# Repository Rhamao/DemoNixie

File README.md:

# DemoNixie
Nouvelle branche du design Android après le merge avec QtBLE.

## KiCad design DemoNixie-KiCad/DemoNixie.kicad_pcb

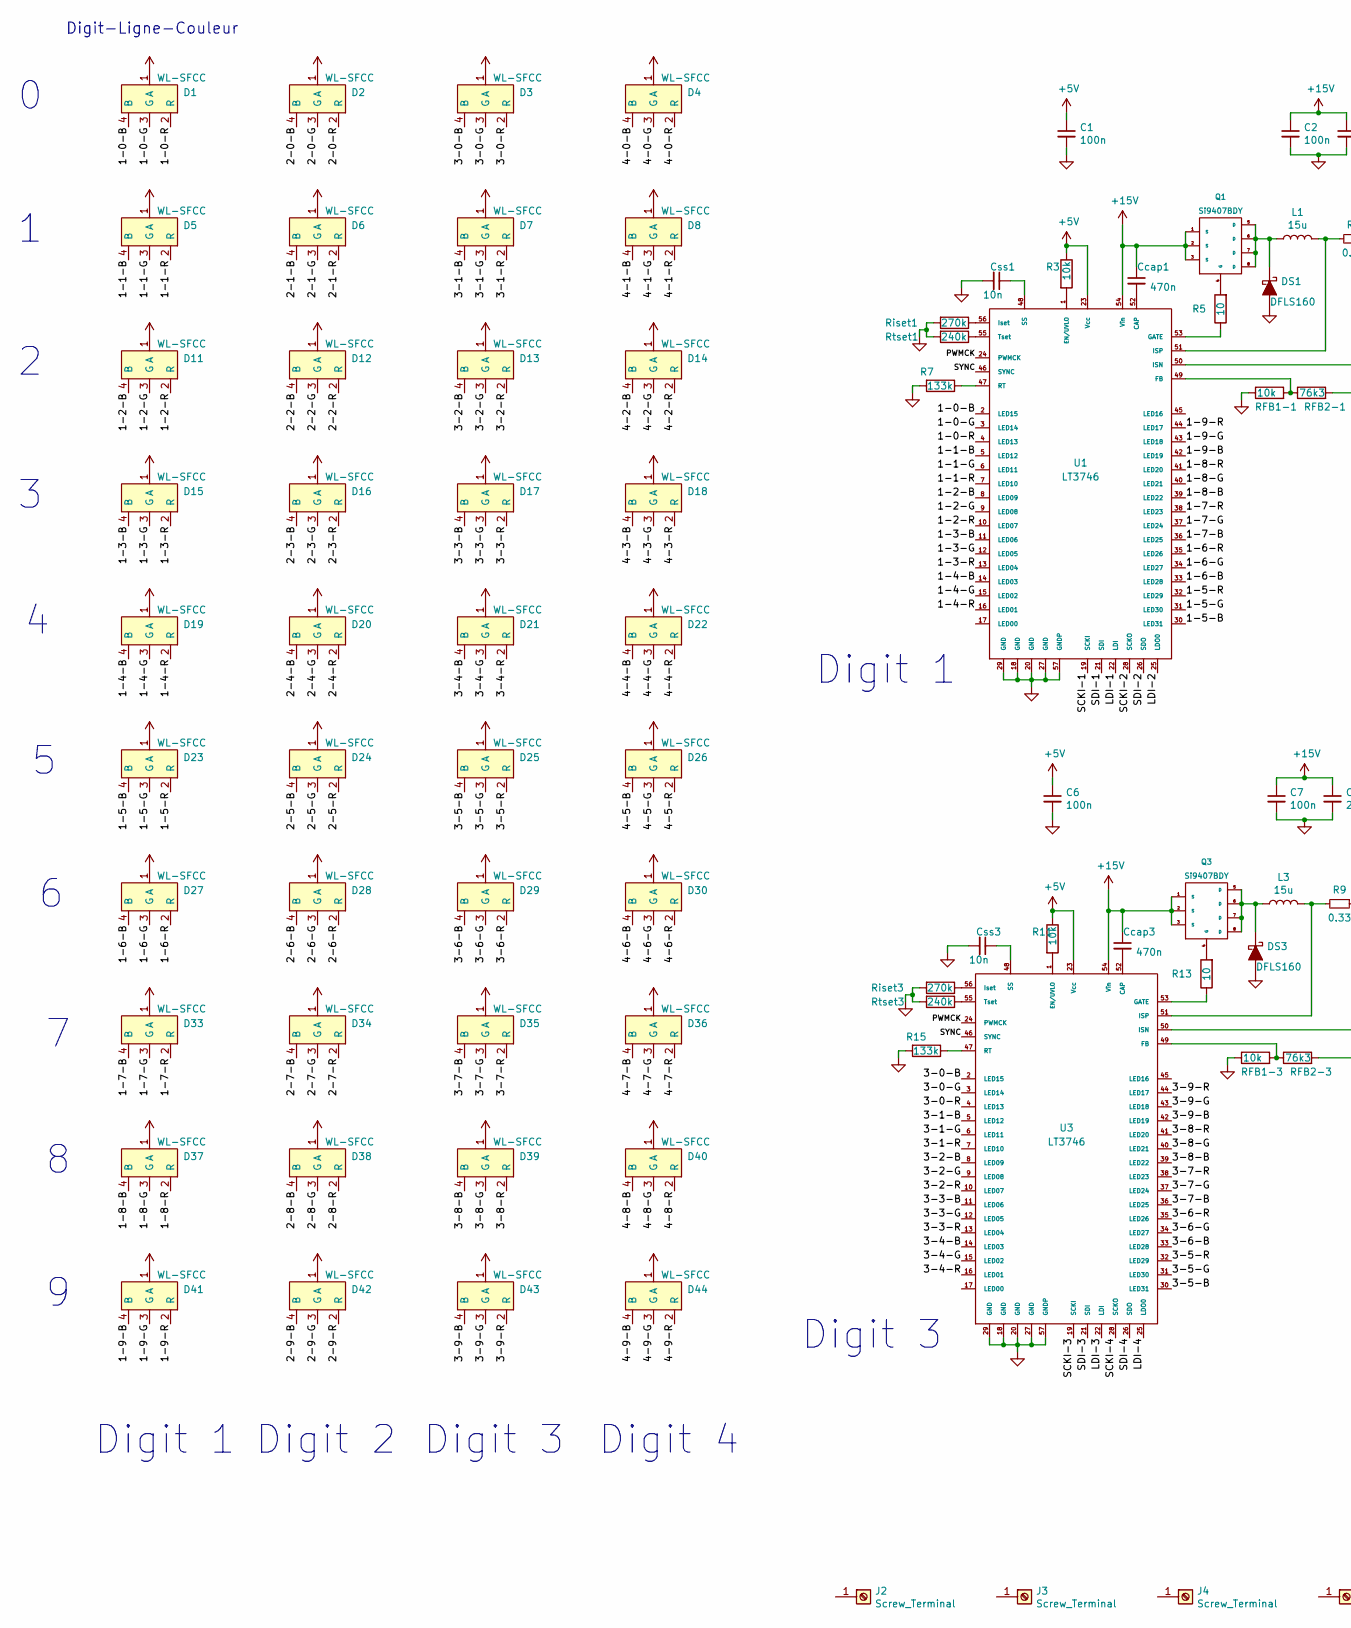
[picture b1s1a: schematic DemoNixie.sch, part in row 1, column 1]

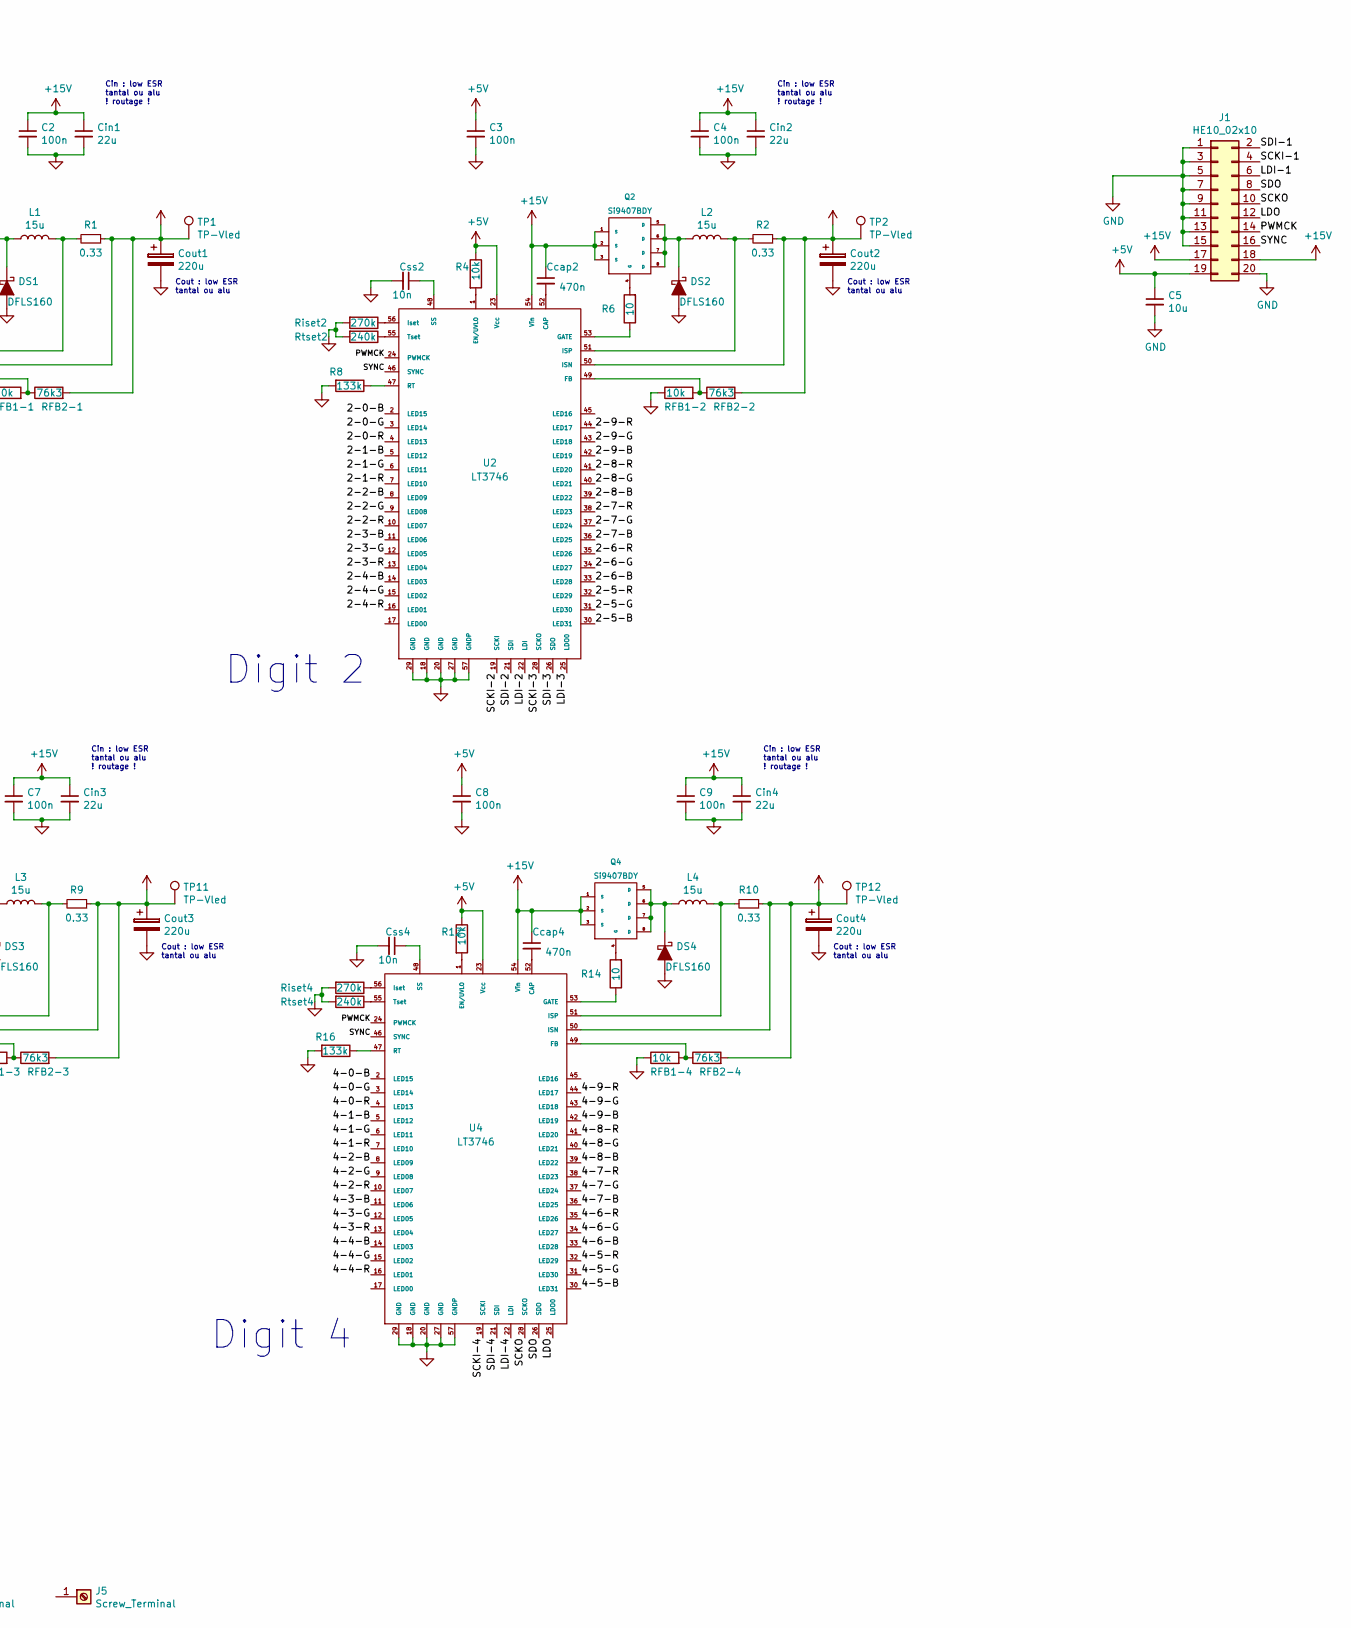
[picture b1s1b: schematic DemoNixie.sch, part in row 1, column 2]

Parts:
C1, C2, C3, C4, C6, C7, C8, C9: 100n; C_0603_1608Metric_Pad1.05x0.95mm_HandSolder
C5: 10u; CP_Elec_6.3x5.9
Ccap1, Ccap2, Ccap3, Ccap4: 470n; C_0603_1608Metric_Pad1.05x0.95mm_HandSolder
Cin1, Cin2, Cin3, Cin4: 22u; CP_Elec_6.3x5.4
Cout1, Cout2, Cout3, Cout4: 220u; CP_Elec_10x14.3
Css1, Css2, Css3, Css4: 10n; C_0603_1608Metric_Pad1.05x0.95mm_HandSolder
D1, D2, D3, D4, D5, D6, D7, D8, D11, D12, D13, D14, D15, D16, D17, D18, D19, D20, D21, D22, D23, D24, D25, D26, D27, D28, D29, D30, D33, D34, D35, D36, D37, D38, D39, D40, D41, D42, D43, D44: WL-SFCC
DS1, DS2, DS3, DS4: DFLS160
J1: HE10_02x10; HE10_2x10_P2.54mm
J2, J3, J4, J5: Screw_Terminal; screwHole3.1mm
L1, L2, L3, L4: 15u; SLF7045-TDK
Q1, Q2, Q3, Q4: Si9407BDY; SOIC-8_3.9x4.9mm_P1.27mm
R1, R2, R9, R10: 0.33; R_0603_1608Metric_Pad1.05x0.95mm_HandSolder
R3, R4, R11, R12: 10k; R_0603_1608Metric_Pad1.05x0.95mm_HandSolder
R5, R6, R13, R14: 10; R_0603_1608Metric_Pad1.05x0.95mm_HandSolder
R7, R8, R15, R16: 133k; R_0603_1608Metric_Pad1.05x0.95mm_HandSolder
RFB1-1, RFB1-2, RFB1-3, RFB1-4: 10k; R_0603_1608Metric_Pad1.05x0.95mm_HandSolder
RFB2-1, RFB2-2, RFB2-3, RFB2-4: 76k3; R_0603_1608Metric_Pad1.05x0.95mm_HandSolder
Riset1, Riset2, Riset3, Riset4: 270k; R_0603_1608Metric_Pad1.05x0.95mm_HandSolder
Rtset1, Rtset2, Rtset3, Rtset4: 240k; R_0603_1608Metric_Pad1.05x0.95mm_HandSolder
TP1, TP2, TP11, TP12: TP-Vled; TestPoint_Pad_D1.5mm
U1, U2, U3, U4: LT3746; LT3746EUHH-TRPBF

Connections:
+5V: C1.1, C3.1, C5.1, C6.1, C8.1, J1.19, R3.1, R4.1, R11.1, R12.1, U1.23 (Vcc), U2.23 (Vcc), U3.23 (Vcc), U4.23 (Vcc)
+15V: C2.1, C4.1, C7.1, C9.1, Ccap1.1, Ccap2.1, Ccap3.1, Ccap4.1, Cin1.1, Cin2.1, Cin3.1, Cin4.1, J1.17, J1.18, Q1.1 (S), Q1.2 (S), Q1.3 (S), Q2.1 (S), Q2.2 (S), Q2.3 (S), Q3.1 (S), Q3.2 (S), Q3.3 (S), Q4.1 (S), Q4.2 (S), Q4.3 (S), U1.54 (Vin), U2.54 (Vin), U3.54 (Vin), U4.54 (Vin)
/1-0-B: D1.4 (B), U1.2 (LED15)
/1-0-G: D1.3 (G), U1.3 (LED14)
/1-0-R: D1.2 (R), U1.4 (LED13)
/1-1-B: D5.4 (B), U1.5 (LED12)
/1-1-G: D5.3 (G), U1.6 (LED11)
/1-1-R: D5.2 (R), U1.7 (LED10)
/1-2-B: D11.4 (B), U1.8 (LED09)
/1-2-G: D11.3 (G), U1.9 (LED08)
/1-2-R: D11.2 (R), U1.10 (LED07)
/1-3-B: D15.4 (B), U1.11 (LED06)
/1-3-G: D15.3 (G), U1.12 (LED05)
/1-3-R: D15.2 (R), U1.13 (LED04)
/1-4-B: D19.4 (B), U1.14 (LED03)
/1-4-G: D19.3 (G), U1.15 (LED02)
/1-4-R: D19.2 (R), U1.16 (LED01)
/1-5-B: D23.4 (B), U1.30 (LED31)
/1-5-G: D23.3 (G), U1.31 (LED30)
/1-5-R: D23.2 (R), U1.32 (LED29)
/1-6-B: D27.4 (B), U1.33 (LED28)
/1-6-G: D27.3 (G), U1.34 (LED27)
/1-6-R: D27.2 (R), U1.35 (LED26)
/1-7-B: D33.4 (B), U1.36 (LED25)
/1-7-G: D33.3 (G), U1.37 (LED24)
/1-7-R: D33.2 (R), U1.38 (LED23)
/1-8-B: D37.4 (B), U1.39 (LED22)
/1-8-G: D37.3 (G), U1.40 (LED21)
/1-8-R: D37.2 (R), U1.41 (LED20)
/1-9-B: D41.4 (B), U1.42 (LED19)
/1-9-G: D41.3 (G), U1.43 (LED18)
/1-9-R: D41.2 (R), U1.44 (LED17)
/2-0-B: D2.4 (B), U2.2 (LED15)
/2-0-G: D2.3 (G), U2.3 (LED14)
/2-0-R: D2.2 (R), U2.4 (LED13)
/2-1-B: D6.4 (B), U2.5 (LED12)
/2-1-G: D6.3 (G), U2.6 (LED11)
/2-1-R: D6.2 (R), U2.7 (LED10)
/2-2-B: D12.4 (B), U2.8 (LED09)
/2-2-G: D12.3 (G), U2.9 (LED08)
/2-2-R: D12.2 (R), U2.10 (LED07)
/2-3-B: D16.4 (B), U2.11 (LED06)
/2-3-G: D16.3 (G), U2.12 (LED05)
/2-3-R: D16.2 (R), U2.13 (LED04)
/2-4-B: D20.4 (B), U2.14 (LED03)
/2-4-G: D20.3 (G), U2.15 (LED02)
/2-4-R: D20.2 (R), U2.16 (LED01)
/2-5-B: D24.4 (B), U2.30 (LED31)
/2-5-G: D24.3 (G), U2.31 (LED30)
/2-5-R: D24.2 (R), U2.32 (LED29)
/2-6-B: D28.4 (B), U2.33 (LED28)
/2-6-G: D28.3 (G), U2.34 (LED27)
/2-6-R: D28.2 (R), U2.35 (LED26)
/2-7-B: D34.4 (B), U2.36 (LED25)
/2-7-G: D34.3 (G), U2.37 (LED24)
/2-7-R: D34.2 (R), U2.38 (LED23)
/2-8-B: D38.4 (B), U2.39 (LED22)
/2-8-G: D38.3 (G), U2.40 (LED21)
/2-8-R: D38.2 (R), U2.41 (LED20)
/2-9-B: D42.4 (B), U2.42 (LED19)
/2-9-G: D42.3 (G), U2.43 (LED18)
/2-9-R: D42.2 (R), U2.44 (LED17)
/3-0-B: D3.4 (B), U3.2 (LED15)
/3-0-G: D3.3 (G), U3.3 (LED14)
/3-0-R: D3.2 (R), U3.4 (LED13)
/3-1-B: D7.4 (B), U3.5 (LED12)
/3-1-G: D7.3 (G), U3.6 (LED11)
/3-1-R: D7.2 (R), U3.7 (LED10)
/3-2-B: D13.4 (B), U3.8 (LED09)
/3-2-G: D13.3 (G), U3.9 (LED08)
/3-2-R: D13.2 (R), U3.10 (LED07)
/3-3-B: D17.4 (B), U3.11 (LED06)
/3-3-G: D17.3 (G), U3.12 (LED05)
/3-3-R: D17.2 (R), U3.13 (LED04)
/3-4-B: D21.4 (B), U3.14 (LED03)
/3-4-G: D21.3 (G), U3.15 (LED02)
/3-4-R: D21.2 (R), U3.16 (LED01)
/3-5-B: D25.4 (B), U3.30 (LED31)
/3-5-G: D25.3 (G), U3.31 (LED30)
/3-5-R: D25.2 (R), U3.32 (LED29)
/3-6-B: D29.4 (B), U3.33 (LED28)
/3-6-G: D29.3 (G), U3.34 (LED27)
/3-6-R: D29.2 (R), U3.35 (LED26)
/3-7-B: D35.4 (B), U3.36 (LED25)
/3-7-G: D35.3 (G), U3.37 (LED24)
/3-7-R: D35.2 (R), U3.38 (LED23)
/3-8-B: D39.4 (B), U3.39 (LED22)
/3-8-G: D39.3 (G), U3.40 (LED21)
/3-8-R: D39.2 (R), U3.41 (LED20)
/3-9-B: D43.4 (B), U3.42 (LED19)
/3-9-G: D43.3 (G), U3.43 (LED18)
/3-9-R: D43.2 (R), U3.44 (LED17)
/4-0-B: D4.4 (B), U4.2 (LED15)
/4-0-G: D4.3 (G), U4.3 (LED14)
/4-0-R: D4.2 (R), U4.4 (LED13)
/4-1-B: D8.4 (B), U4.5 (LED12)
/4-1-G: D8.3 (G), U4.6 (LED11)
/4-1-R: D8.2 (R), U4.7 (LED10)
/4-2-B: D14.4 (B), U4.8 (LED09)
/4-2-G: D14.3 (G), U4.9 (LED08)
/4-2-R: D14.2 (R), U4.10 (LED07)
/4-3-B: D18.4 (B), U4.11 (LED06)
/4-3-G: D18.3 (G), U4.12 (LED05)
/4-3-R: D18.2 (R), U4.13 (LED04)
/4-4-B: D22.4 (B), U4.14 (LED03)
/4-4-G: D22.3 (G), U4.15 (LED02)
/4-4-R: D22.2 (R), U4.16 (LED01)
/4-5-B: D26.4 (B), U4.30 (LED31)
/4-5-G: D26.3 (G), U4.31 (LED30)
/4-5-R: D26.2 (R), U4.32 (LED29)
/4-6-B: D30.4 (B), U4.33 (LED28)
/4-6-G: D30.3 (G), U4.34 (LED27)
/4-6-R: D30.2 (R), U4.35 (LED26)
/4-7-B: D36.4 (B), U4.36 (LED25)
/4-7-G: D36.3 (G), U4.37 (LED24)
/4-7-R: D36.2 (R), U4.38 (LED23)
/4-8-B: D40.4 (B), U4.39 (LED22)
/4-8-G: D40.3 (G), U4.40 (LED21)
/4-8-R: D40.2 (R), U4.41 (LED20)
/4-9-B: D44.4 (B), U4.42 (LED19)
/4-9-G: D44.3 (G), U4.43 (LED18)
/4-9-R: D44.2 (R), U4.44 (LED17)
/LDI-1: J1.6, U1.22 (LDI)
/LDI-2: U1.25 (LDO0), U2.22 (LDI)
/LDI-3: U2.25 (LDO0), U3.22 (LDI)
/LDI-4: U3.25 (LDO0), U4.22 (LDI)
/LDO: J1.12, U4.25 (LDO0)
/PWMCK: J1.14, U1.24 (PWMCK), U2.24 (PWMCK), U3.24 (PWMCK), U4.24 (PWMCK)
/SCKI-1: J1.4, U1.19 (SCKI)
/SCKI-2: U1.28 (SCKO), U2.19 (SCKI)
/SCKI-3: U2.28 (SCKO), U3.19 (SCKI)
/SCKI-4: U3.28 (SCKO), U4.19 (SCKI)
/SCKO: J1.10, U4.28 (SCKO)
/SDI-1: J1.2, U1.21 (SDI)
/SDI-2: U1.26 (SDO), U2.21 (SDI)
/SDI-3: U2.26 (SDO), U3.21 (SDI)
/SDI-4: U3.26 (SDO), U4.21 (SDI)
/SDO: J1.8, U4.26 (SDO)
/SYNC: J1.16, U1.46 (SYNC), U2.46 (SYNC), U3.46 (SYNC), U4.46 (SYNC)
GND: C1.2, C2.2, C3.2, C4.2, C5.2, C6.2, C7.2, C8.2, C9.2, Cin1.2, Cin2.2, Cin3.2, Cin4.2, Cout1.2, Cout2.2, Cout3.2, Cout4.2, Css1.2, Css2.2, Css3.2, Css4.2, DS1.2 (A), DS2.2 (A), DS3.2 (A), DS4.2 (A), J1.1, J1.3, J1.5, J1.7, J1.9, J1.11, J1.13, J1.15, J1.20, R7.2, R8.2, R15.2, R16.2, RFB1-1.1, RFB1-2.1, RFB1-3.1, RFB1-4.1, Riset1.2, Riset2.2, Riset3.2, Riset4.2, Rtset1.2, Rtset2.2, Rtset3.2, Rtset4.2, U1.18 (GND), U1.20 (GND), U1.27 (GND), U1.29 (GND), U1.57 (GNDP), U2.18 (GND), U2.20 (GND), U2.27 (GND), U2.29 (GND), U2.57 (GNDP), U3.18 (GND), U3.20 (GND), U3.27 (GND), U3.29 (GND), U3.57 (GNDP), U4.18 (GND), U4.20 (GND), U4.27 (GND), U4.29 (GND), U4.57 (GNDP)
unnamed: Ccap1.2, U1.52 (CAP)
unnamed: Ccap2.2, U2.52 (CAP)
unnamed: Ccap3.2, U3.52 (CAP)
unnamed: Ccap4.2, U4.52 (CAP)
unnamed: Css1.1, U1.48 (SS)
unnamed: Css2.1, U2.48 (SS)
unnamed: Css3.1, U3.48 (SS)
unnamed: Css4.1, U4.48 (SS)
unnamed: DS1.1 (K), L1.1, Q1.5 (D), Q1.6 (D), Q1.7 (D), Q1.8 (D)
unnamed: DS2.1 (K), L2.1, Q2.5 (D), Q2.6 (D), Q2.7 (D), Q2.8 (D)
unnamed: DS3.1 (K), L3.1, Q3.5 (D), Q3.6 (D), Q3.7 (D), Q3.8 (D)
unnamed: DS4.1 (K), L4.1, Q4.5 (D), Q4.6 (D), Q4.7 (D), Q4.8 (D)
unnamed: L1.2, R1.2, U1.51 (ISP)
unnamed: L2.2, R2.2, U2.51 (ISP)
unnamed: L3.2, R9.2, U3.51 (ISP)
unnamed: L4.2, R10.2, U4.51 (ISP)
unnamed: Q1.4 (G), R5.2
unnamed: Q2.4 (G), R6.2
unnamed: Q3.4 (G), R13.2
unnamed: Q4.4 (G), R14.2
unnamed: R3.2, U1.1 (EN/UVLO)
unnamed: R4.2, U2.1 (EN/UVLO)
unnamed: R5.1, U1.53 (GATE)
unnamed: R6.1, U2.53 (GATE)
unnamed: R7.1, U1.47 (RT)
unnamed: R8.1, U2.47 (RT)
unnamed: R11.2, U3.1 (EN/UVLO)
unnamed: R12.2, U4.1 (EN/UVLO)
unnamed: R13.1, U3.53 (GATE)
unnamed: R14.1, U4.53 (GATE)
unnamed: R15.1, U3.47 (RT)
unnamed: R16.1, U4.47 (RT)
unnamed: RFB1-1.2, RFB2-1.1, U1.49 (FB)
unnamed: RFB1-2.2, RFB2-2.1, U2.49 (FB)
unnamed: RFB1-3.2, RFB2-3.1, U3.49 (FB)
unnamed: RFB1-4.2, RFB2-4.1, U4.49 (FB)
unnamed: Riset1.1, U1.56 (Iset)
unnamed: Riset2.1, U2.56 (Iset)
unnamed: Riset3.1, U3.56 (Iset)
unnamed: Riset4.1, U4.56 (Iset)
unnamed: Rtset1.1, U1.55 (Tset)
unnamed: Rtset2.1, U2.55 (Tset)
unnamed: Rtset3.1, U3.55 (Tset)
unnamed: Rtset4.1, U4.55 (Tset)
VPP: Cout1.1, Cout2.1, Cout3.1, Cout4.1, D1.1 (A), D2.1 (A), D3.1 (A), D4.1 (A), D5.1 (A), D6.1 (A), D7.1 (A), D8.1 (A), D11.1 (A), D12.1 (A), D13.1 (A), D14.1 (A), D15.1 (A), D16.1 (A), D17.1 (A), D18.1 (A), D19.1 (A), D20.1 (A), D21.1 (A), D22.1 (A), D23.1 (A), D24.1 (A), D25.1 (A), D26.1 (A), D27.1 (A), D28.1 (A), D29.1 (A), D30.1 (A), D33.1 (A), D34.1 (A), D35.1 (A), D36.1 (A), D37.1 (A), D38.1 (A), D39.1 (A), D40.1 (A), D41.1 (A), D42.1 (A), D43.1 (A), D44.1 (A), R1.1, R2.1, R9.1, R10.1, RFB2-1.2, RFB2-2.2, RFB2-3.2, RFB2-4.2, TP1.1, TP2.1, TP11.1, TP12.1, U1.50 (ISN), U2.50 (ISN), U3.50 (ISN), U4.50 (ISN)

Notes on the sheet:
Digit 1
Digit 2
Digit 3
Digit 4
Digit-Ligne-Couleur
Cout : low ESR tantal ou alu
Cin : low ESR tantal ou alu ! routage !

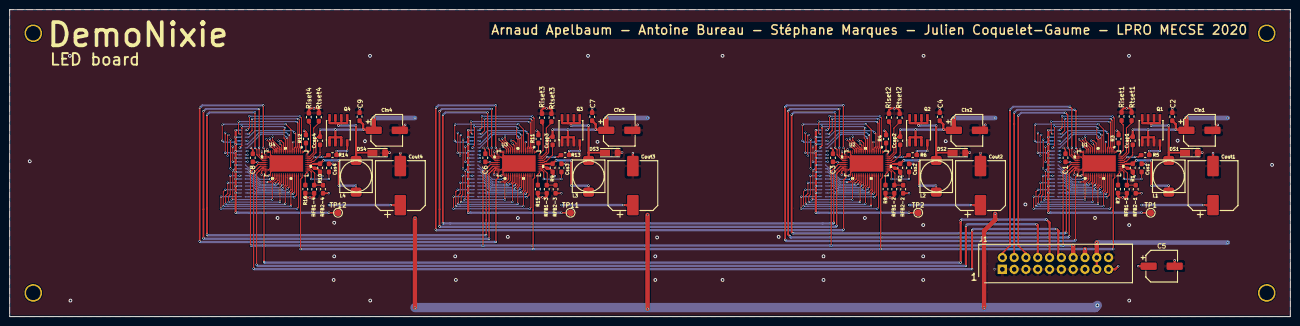
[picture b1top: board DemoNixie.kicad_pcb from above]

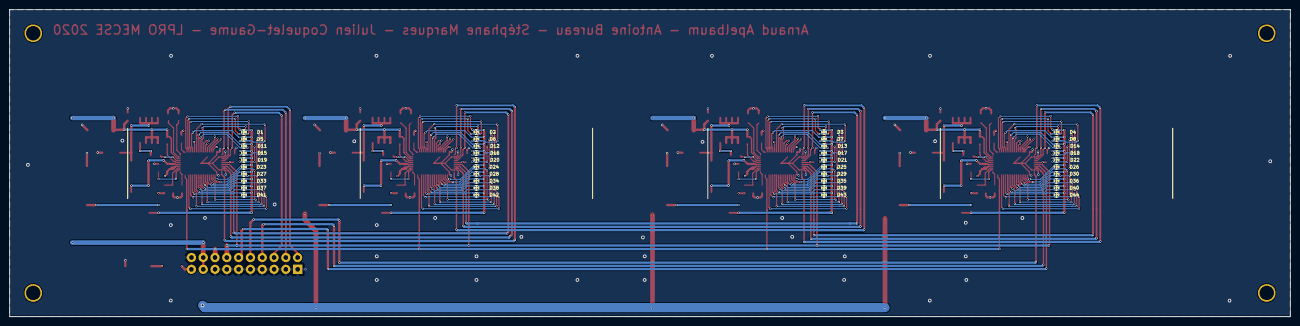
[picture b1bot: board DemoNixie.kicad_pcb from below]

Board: 4 copper layers, 275.6 x 66.0 mm, 122 parts (40 on the bottom side), 185 nets.

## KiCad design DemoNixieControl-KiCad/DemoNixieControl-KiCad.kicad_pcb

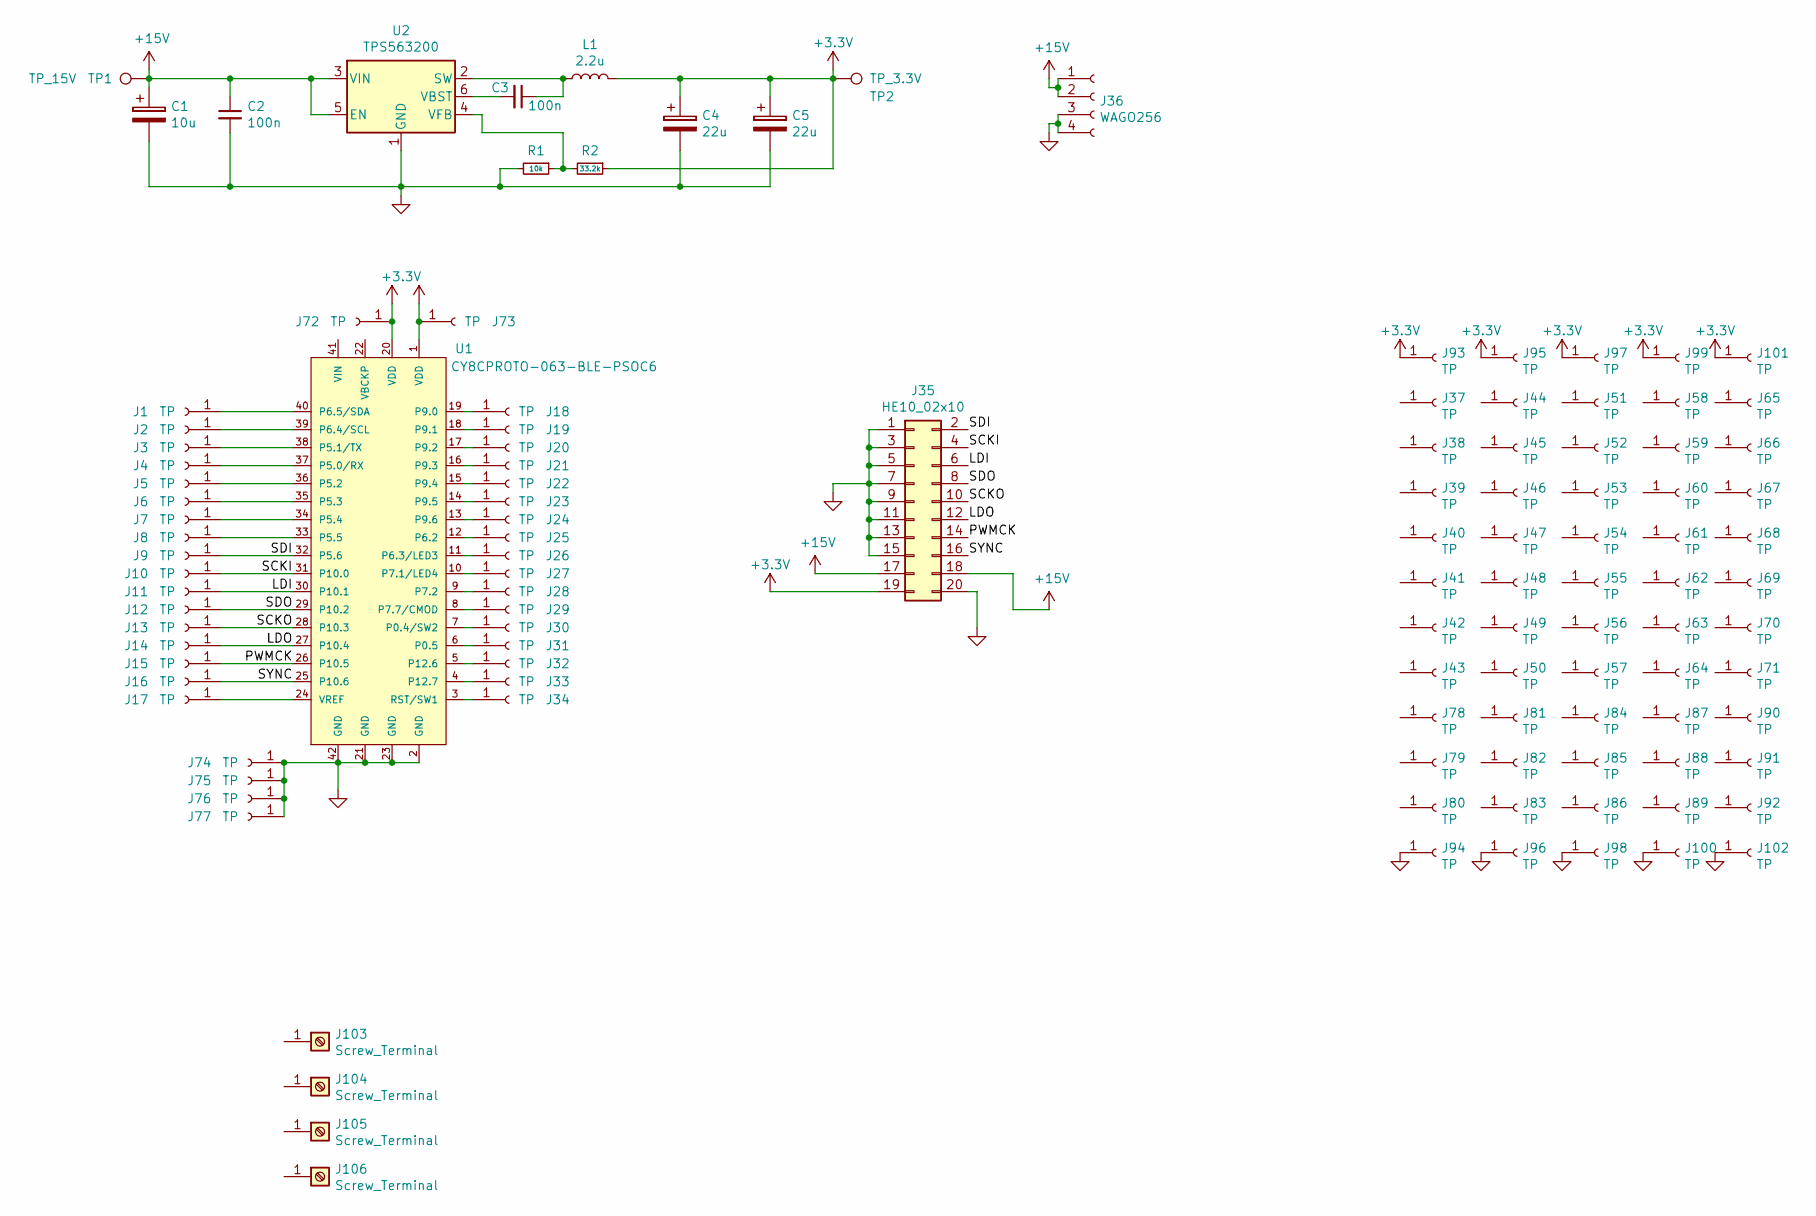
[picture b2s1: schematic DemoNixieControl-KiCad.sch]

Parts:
C1: 10u; CP_Elec_6.3x5.9
C2, C3: 100n; C_0603_1608Metric_Pad1.05x0.95mm_HandSolder
C4, C5: 22u; CP_Elec_6.3x5.4
J1, J2, J3, J4, J5, J6, J7, J8, J9, J10, J11, J12, J13, J14, J15, J16, J17, J18, J19, J20, J21, J22, J23, J24, J25, J26, J27, J28, J29, J30, J31, J32, J33, J34, J37, J38, J39, J40, J41, J42, J43, J44, J45, J46, J47, J48, J49, J50, J51, J52, J53, J54, J55, J56, J57, J58, J59, J60, J61, J62, J63, J64, J65, J66, J67, J68, J69, J70, J71, J72, J73, J74, J75, J76, J77, J78, J79, J80, J81, J82, J83, J84, J85, J86, J87, J88, J89, J90, J91, J92, J93, J94, J95, J96, J97, J98, J99, J100, J101, J102: TP; PIN-tr1-d2
J35: HE10_02x10; HE10_2x10_P2.54mm
J36: WAGO256; WAGO-256-402
J103, J104, J105, J106: Screw_Terminal; screwHole3.1mm
L1: 2.2u; 744778002 Wurth
R1: 10k; R_0603_1608Metric_Pad1.05x0.95mm_HandSolder
R2: 33.2k; R_1206_3216Metric_Pad1.42x1.75mm_HandSolder
TP1: TP_15V; TestPoint_Loop_D1.80mm_Drill1.0mm_Beaded
TP2: TP_3.3V; TestPoint_Loop_D1.80mm_Drill1.0mm_Beaded
U1: CY8CPROTO-063-BLE-PSOC6; CY8CPROTO-063-BLE
U2: TPS563200; SOT-23-6_Handsoldering

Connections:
+3V3: C4.1, C5.1, J35.19, J72.1, J73.1, J93.1, J95.1, J97.1, J99.1, J101.1, L1.2, R2.1, TP2.1, U1.1 (VDD), U1.20 (VDD)
+15V: C1.1, C2.1, J35.17, J35.18, J36.1, J36.2, TP1.1, U2.3 (VIN), U2.5 (EN)
/LDI: J11.1, J35.6, U1.30 (P10.1)
/LDO: J14.1, J35.12, U1.27 (P10.4)
/PWMCK: J15.1, J35.14, U1.26 (P10.5)
/SCKI: J10.1, J35.4, U1.31 (P10.0)
/SCKO: J13.1, J35.10, U1.28 (P10.3)
/SDI: J9.1, J35.2, U1.32 (P5.6)
/SDO: J12.1, J35.8, U1.29 (P10.2)
/SYNC: J16.1, J35.16, U1.25 (P10.6)
GND: C1.2, C2.2, C4.2, C5.2, J35.1, J35.3, J35.5, J35.7, J35.9, J35.11, J35.13, J35.15, J35.20, J36.3, J36.4, J74.1, J75.1, J76.1, J77.1, J94.1, J96.1, J98.1, J100.1, J102.1, R1.2, U1.2 (GND), U1.21 (GND), U1.23 (GND), U1.42 (GND), U2.1 (GND)
unnamed: C3.1, L1.1, U2.2 (SW)
unnamed: C3.2, U2.6 (VBST)
unnamed: J1.1, U1.40 (P6.5/SDA)
unnamed: J2.1, U1.39 (P6.4/SCL)
unnamed: J3.1, U1.38 (P5.1/TX)
unnamed: J4.1, U1.37 (P5.0/RX)
unnamed: J5.1, U1.36 (P5.2)
unnamed: J6.1, U1.35 (P5.3)
unnamed: J7.1, U1.34 (P5.4)
unnamed: J8.1, U1.33 (P5.5)
unnamed: J17.1, U1.24 (VREF)
unnamed: J18.1, U1.19 (P9.0)
unnamed: J19.1, U1.18 (P9.1)
unnamed: J20.1, U1.17 (P9.2)
unnamed: J21.1, U1.16 (P9.3)
unnamed: J22.1, U1.15 (P9.4)
unnamed: J23.1, U1.14 (P9.5)
unnamed: J24.1, U1.13 (P9.6)
unnamed: J25.1, U1.12 (P6.2)
unnamed: J26.1, U1.11 (P6.3/LED3)
unnamed: J27.1, U1.10 (P7.1/LED4)
unnamed: J28.1, U1.9 (P7.2)
unnamed: J29.1, U1.8 (P7.7/CMOD)
unnamed: J30.1, U1.7 (P0.4/SW2)
unnamed: J31.1, U1.6 (P0.5)
unnamed: J32.1, U1.5 (P12.6)
unnamed: J33.1, U1.4 (P12.7)
unnamed: J34.1, U1.3 (RST/SW1)
unnamed: R1.1, R2.2, U2.4 (VFB)

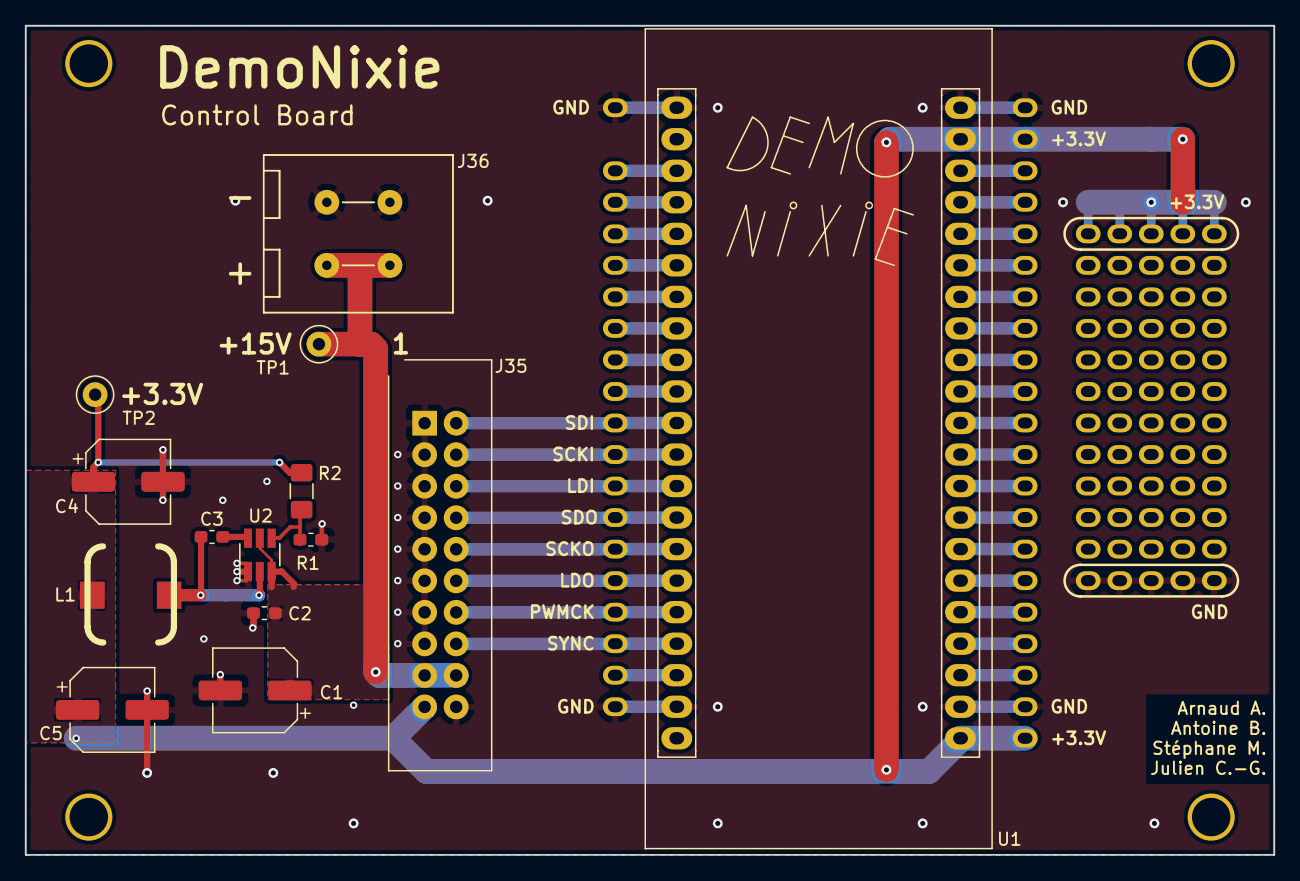
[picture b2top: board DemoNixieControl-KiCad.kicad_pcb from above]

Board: 2 copper layers, 100.6 x 66.8 mm, 118 parts (0 on the bottom side), 40 nets.

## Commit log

2020-02-27 added led
2020-02-27 add led doc
2020-02-27 add uc doc
2020-02-27 materiel.md
    Liste du matériel pour le projet
2020-02-27 Delete materiel.md
    Useless file
2020-02-27 Add files via upload
    Score scrum et répartition des sprints
2020-05-04 Add files via upload
    Inventaire au 04 05 2020
2020-05-04 Add files via upload
    Inventaire au 04/05/2020
2020-05-05 add digit drawing
2020-05-11 structure du projet
2020-05-11 Création d'une branche pour déposer tous les documents qui ne sont PAS DES PROJETS DE PROGRAMATION. Cette branche ne sera donc jamais merge sur la principale, elle sert uniquement à recevoir des docu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
2020-05-11 Retrait des documents et des exemples de codes qui sont transférés sur les bracnhes 'documents_divers' et 'exemples_de_codes'
2020-05-11 protocole BLE
2020-05-11 Retrait du dossier DemoNixie transféré sur la branche 'exemples_de_codes'
2020-05-11 Update README.md
    MàJ infos sur les nouvelles branches
2020-05-11 Update README.md
    Ajout des sauts de ligne manquants
2020-05-14 Crétaion de la branche du design de l'app Android en QML.
2020-05-14 Premiere essai d'interface : pallette et temps + essai changement de l'heure
2020-05-17 add doc LT3746
2020-05-17 demo-schema-lt3746
2020-05-18 Création des objest ScrcollableClock et ScrollableNumber pour corriger les problèmes de positionement des chiffres avec l'objet ListView.
2020-06-03 Horloge scrollable callé sur le temps réel, reste à passer du début à la fin des listview de façon instané sur un changement de minutes, heures ou secondes
2020-06-03 Correction du pbe de listview, on passe maintenant directeent du de la fin (59s ou 59min ou 23h) au début des listViews (0s, 0min, 0h)
2020-06-05 debug View
2020-06-05 Création de l'objet DemoNixieButton pour génére les boutons de l'app
2020-06-05 Correction de la taille de l'horloge et du non-aignement avec les 2 points
2020-06-08 Copie du temps réel directement dans SrollableClock au lieu du main + tentative infrutueuse de régler tous les problèmes de l'affichage du temps en scrolling à l'ouverture/fermeture de l'application
2020-06-08 L'heure ne défile plus dans ScrollableCLock mais peut toujours êter modfifier par scroll, cela évite un conflit entre le set instantané de l'heure au lancement/relancement de l'app et le défilement d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
2020-06-09 creation de la branche
2020-06-09 Update README.md
    Correction de la description du ReadMe
2020-06-09 Update README.md
    MàJ des descriptiions des branches
2020-06-09 finalisation controlBoard
2020-06-09 Ajout de la fonction de <set time> sans la correction de l'offset (prévu pour le prochain commit)
2020-06-09 Correction de tous les problemes de défilement de l'heure.
2020-06-10 Fonctionalité <set time> fonctionelle
2020-06-10 Ajout fonctionalité <reset time>
2020-06-10 ajout des cotes des cartes
2020-06-10 Ajout bouton/voyant bluetooth + bouton envoi trame bluetooth
2020-06-11 Changement de la classe DemoNixieButton pour insérer le texte et les images proprement
2020-06-12 Ajout du backend c++ à ScrollableClock pour pouvoir rajouter le propriété UTC qui permet de changer la chréneau horaire
2020-06-12 Le paramètre utc n'est maintenant pris en compte que dans l'intervalle -12 à +14 et les dépassements de temps (supérieur à 24h et inférieur à 0h) sont traités correctement
2020-06-12 Set UTC fonctionel
2020-06-12 Le texte du bouton setUtcButton change pour les chrono horaires positifs et négatifs
2020-06-12 Ajout de la méthode resetLocalTime() dans ScrollableCLock + le bouton 'reset' reset maintenant l'heure à l'heure locale ainsi que le chréneau horaire (utc) au chréneau horraire local + correction d'u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
2020-06-15 ajout fichier de commande RS
2020-06-16 Changement des couleurs fonctionnels sur mobiles
2020-06-16 Changement des couleurs fonctionnels sur mobiles + retrait de ColorSelector obselète
2020-06-16 Amélioration esthétique du changement de couleur
2020-06-16 Le bouton UTC affiche désormais 'UTC\n+?' si qqn a chnagé l'heure manuellement
2020-06-17 QQes corrections sur le changement de couleur
2020-06-18 enfin git add .!
2020-06-18 Correction uint -> int
2020-06-19 Correction de la config des fichiers header -> le projet est fonctionnel
2020-06-23 Ajout des fonctions bluetooth à l'interface principale + ajout des messages toast dans la classe dbglink sous compilateur android
2020-06-23 Creation de du signal newText pour avoir des messages uniques a afficher par toast message
2020-06-25 update connection process
2020-06-25 changement de branche
2020-06-25 Retour sur la branche design Android
2020-06-25 Retour sur la branche design_android
2020-06-25 Premiere version finie de l'interface, beta testage realises, tous les bugs trouves ont ete corriges
2020-06-25 Correction du nom de l'app, ajout du logo et orientation portrait
2020-06-26 new Version

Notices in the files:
parts and their libraries:
Copyright 2016 Accelerated Designs. All rights reserved.
